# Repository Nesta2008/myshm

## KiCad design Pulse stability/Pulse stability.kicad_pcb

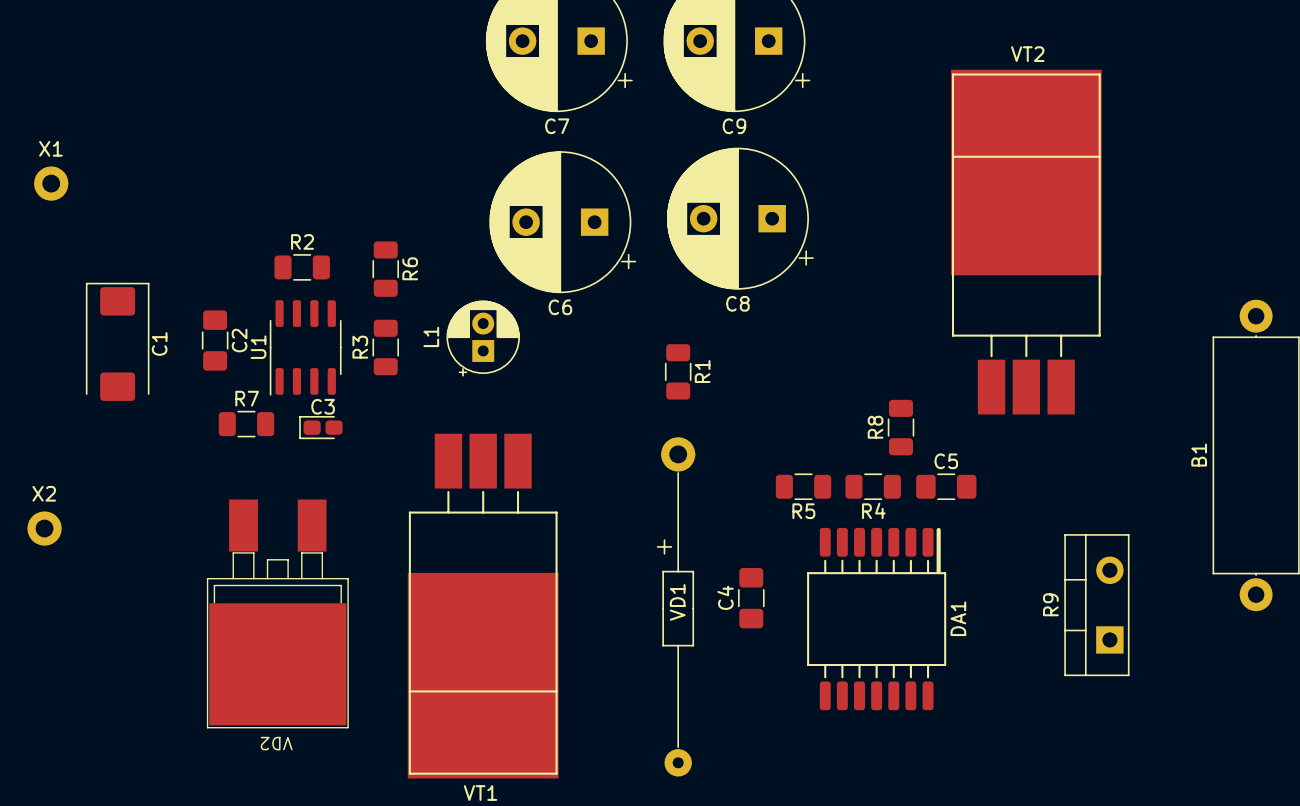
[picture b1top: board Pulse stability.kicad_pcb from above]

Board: 2 copper layers, 28 parts (0 on the bottom side), 16 nets, no tracks yet.

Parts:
B1: thermocouple; R_Axial_DIN0617_L17.0mm_D6.0mm_P20.32mm_Horizontal
C1: 15; CP_EIA-7343-40_Kemet-Y
C2, C4, C5: 0.15; C_1206_3216Metric_Pad1.42x1.75mm_HandSolder
C3: 8p; CP_EIA-1608-08_AVX-J_Pad1.25x1.05mm_HandSolder
C6, C7, C8, C9: 680; CP_Radial_D10.0mm_P5.00mm
DA1: 1486УД3; 401.14-5
L1: 27мк; CP_Radial_D5.0mm_P2.00mm
R1, R4: 510; R_1206_3216Metric
R2: 0.5; R_1206_3216Metric
R3: 12.5k; R_1206_3216Metric
R5: 360; R_1206_3216Metric
R6: 107.5k; R_1206_3216Metric
R7, R8: 1k; R_1206_3216Metric
R9: 1 Ом 20 Вт; TO-220-2_Vertical
U1: MC34063ABD-TR; SOIC-8_3.9x4.9mm_P1.27mm
VD1: Д818Е; Д818Д_P22.50mm_Pad0.8mm
VD2: VD_Schottky; КТ-90
VT1, VT2: КТ805АМ; КТ-28А-2.02_Horizontal_smd
X1: +27V; 2,5x1,3
X2: -27V; 2,5x1,3

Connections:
+12V: C5.1, C6.1, C7.1, C8.1, C9.1, DA1.4, L1.2, R1.1, R6.1
+27V: C1.1, C2.1, R2.2, U1.6, X1.1
GND: C1.2, C2.2, C3.2, C4.2, C5.2, C6.2, C7.2, C8.2, C9.2, DA1.7, DA1.8, DA1.11, DA1.14, R3.1, R5.2, R7.1, R9.2, U1.2, U1.4, VD1.2, VD2.2, X2.1
unnamed: C3.1, U1.3
unnamed: C4.1, R1.2, R4.1, VD1.1
unnamed: DA1.1, R8.1
unnamed: DA1.2, R9.1, VT2.2
unnamed: DA1.3, R4.2, R5.1
unnamed: DA1.5, DA1.6
unnamed: DA1.9, DA1.10
unnamed: DA1.12, DA1.13
unnamed: L1.1, VD2.1, VT1.2
unnamed: R2.1, U1.7, VT1.3
unnamed: R3.2, R6.2, U1.5
unnamed: R7.2, U1.1, U1.8, VT1.1
unnamed: R8.2, VT2.1

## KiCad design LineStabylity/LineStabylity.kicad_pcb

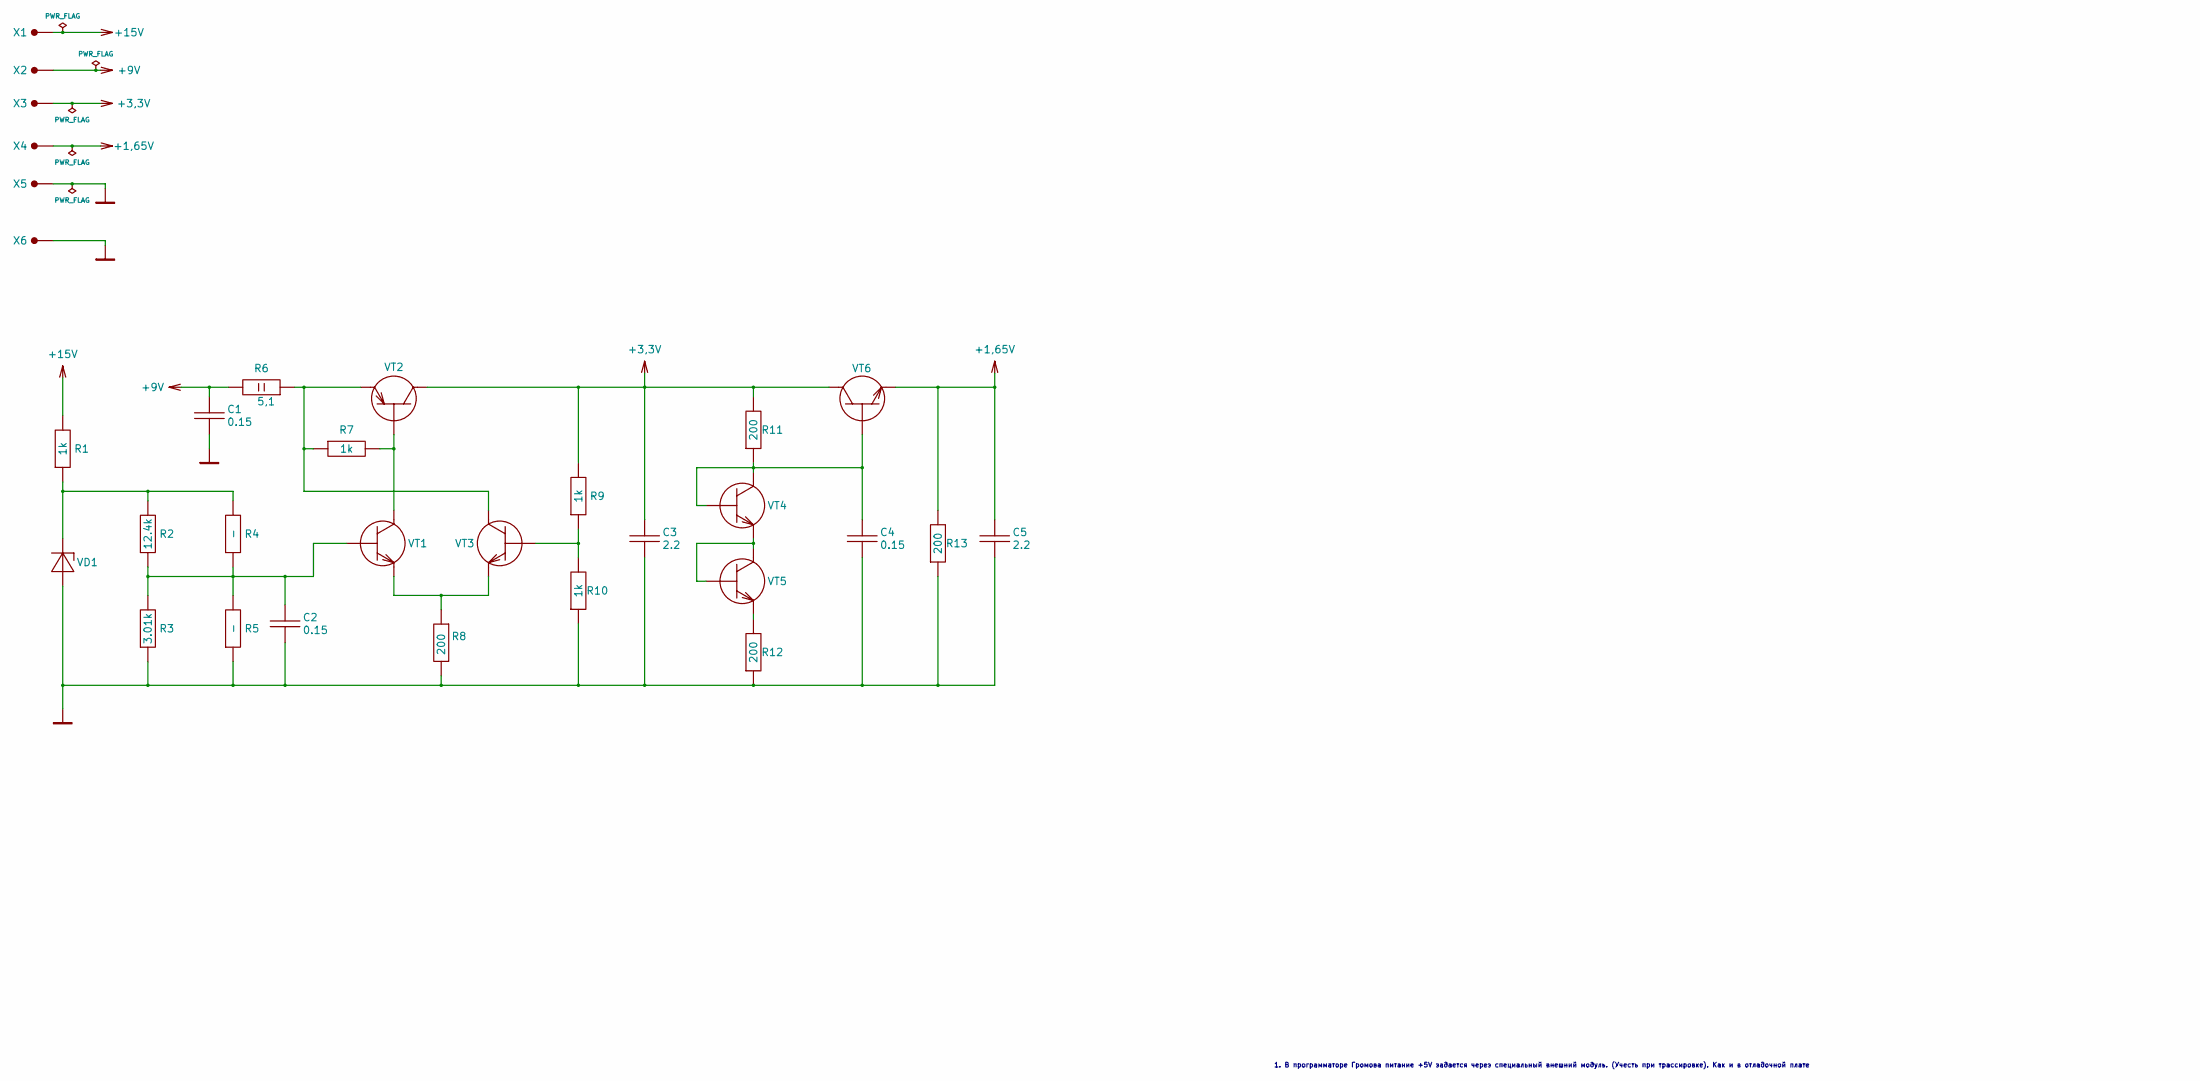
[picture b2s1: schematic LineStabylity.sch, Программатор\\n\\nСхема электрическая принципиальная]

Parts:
C1, C2, C4: 0.15; C_0805_2012Metric_Pad1.15x1.40mm_HandSolder
C3, C5: 2.2; C_2220_5650Metric
R1, R7, R9, R10: 1k; R_0805_2012Metric_Pad1.15x1.40mm_HandSolder
R2: 12.4k; R_0805_2012Metric_Pad1.15x1.40mm_HandSolder
R3: 3.01k; R_0805_2012Metric_Pad1.15x1.40mm_HandSolder
R4, R5: -; R_0805_2012Metric_Pad1.15x1.40mm_HandSolder
R6: 5,1; R_4020_10251Metric
R8, R11, R12, R13: 200; R_0805_2012Metric_Pad1.15x1.40mm_HandSolder
VD1: Д818Е; D_DO-15_P12.70mm_Horizontal
VT1, VT3, VT4, VT5, VT6: 2Т3130А9; SOT-23
VT2: 2Т664А9; SOT-89-3
X1, X2, X3, X4, X5, X6: CON; SolderWirePad_single_2.5x1.3mmDrill

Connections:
+1,65V: C5.1, R13.2, VT6.2 (E), X4.1
+3,3V: C3.1, R9.2, R11.2, VT2.2 (C), VT6.3 (C), X3.1
+9V: C1.1, R6.2, X2.1
+15V: R1.2, X1.1
GND: C1.2, C2.2, C3.2, C4.2, C5.2, R3.1, R5.1, R8.2, R10.1, R12.1, R13.1, VD1.2 (A), X5.1, X6.1
unnamed: C2.1, R2.1, R3.2, R4.1, R5.2, VT1.1 (B)
unnamed: C4.1, R11.1, VT4.1 (B), VT4.3 (C), VT6.1 (B)
unnamed: R1.1, R2.2, R4.2, VD1.1 (K)
unnamed: R6.1, R7.1, VT2.3 (E), VT3.3 (C)
unnamed: R7.2, VT1.3 (C), VT2.1 (B)
unnamed: R8.1, VT1.2 (E), VT3.2 (E)
unnamed: R9.1, R10.2, VT3.1 (B)
unnamed: R12.2, VT5.2 (E)
unnamed: VT4.2 (E), VT5.1 (B), VT5.3 (C)

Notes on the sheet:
1. В программаторе Громова питание +5V задается через специальный внешний модуль. (Учесть при трассировке). Как и в отладочной плате

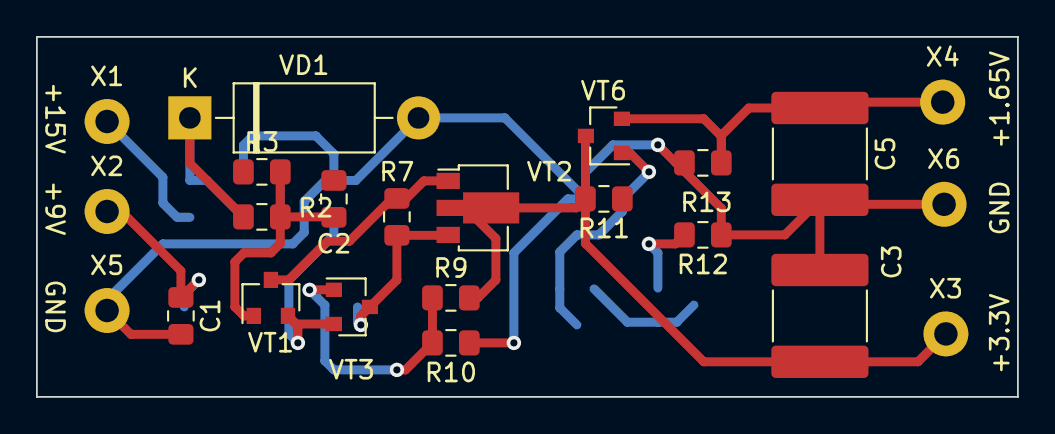
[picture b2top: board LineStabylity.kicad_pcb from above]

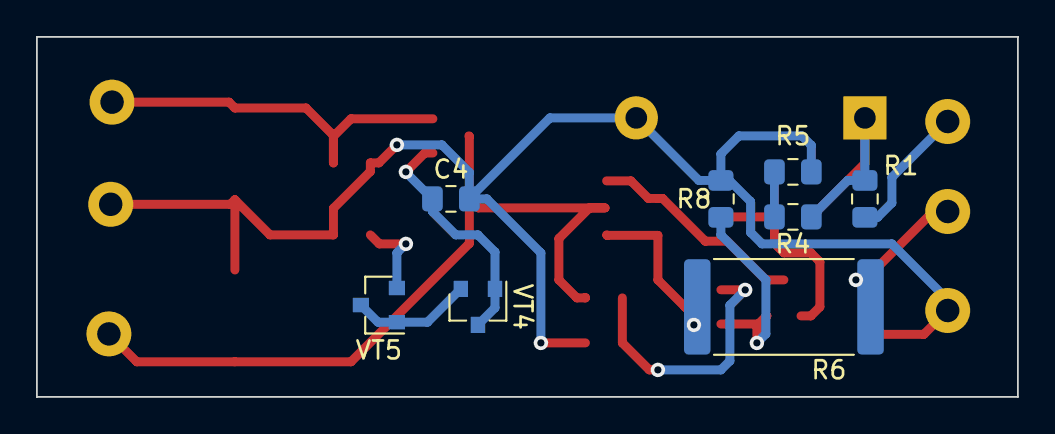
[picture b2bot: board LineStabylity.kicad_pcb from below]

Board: 2 copper layers, 54.5 x 20.0 mm, 31 parts (8 on the bottom side), 14 nets.

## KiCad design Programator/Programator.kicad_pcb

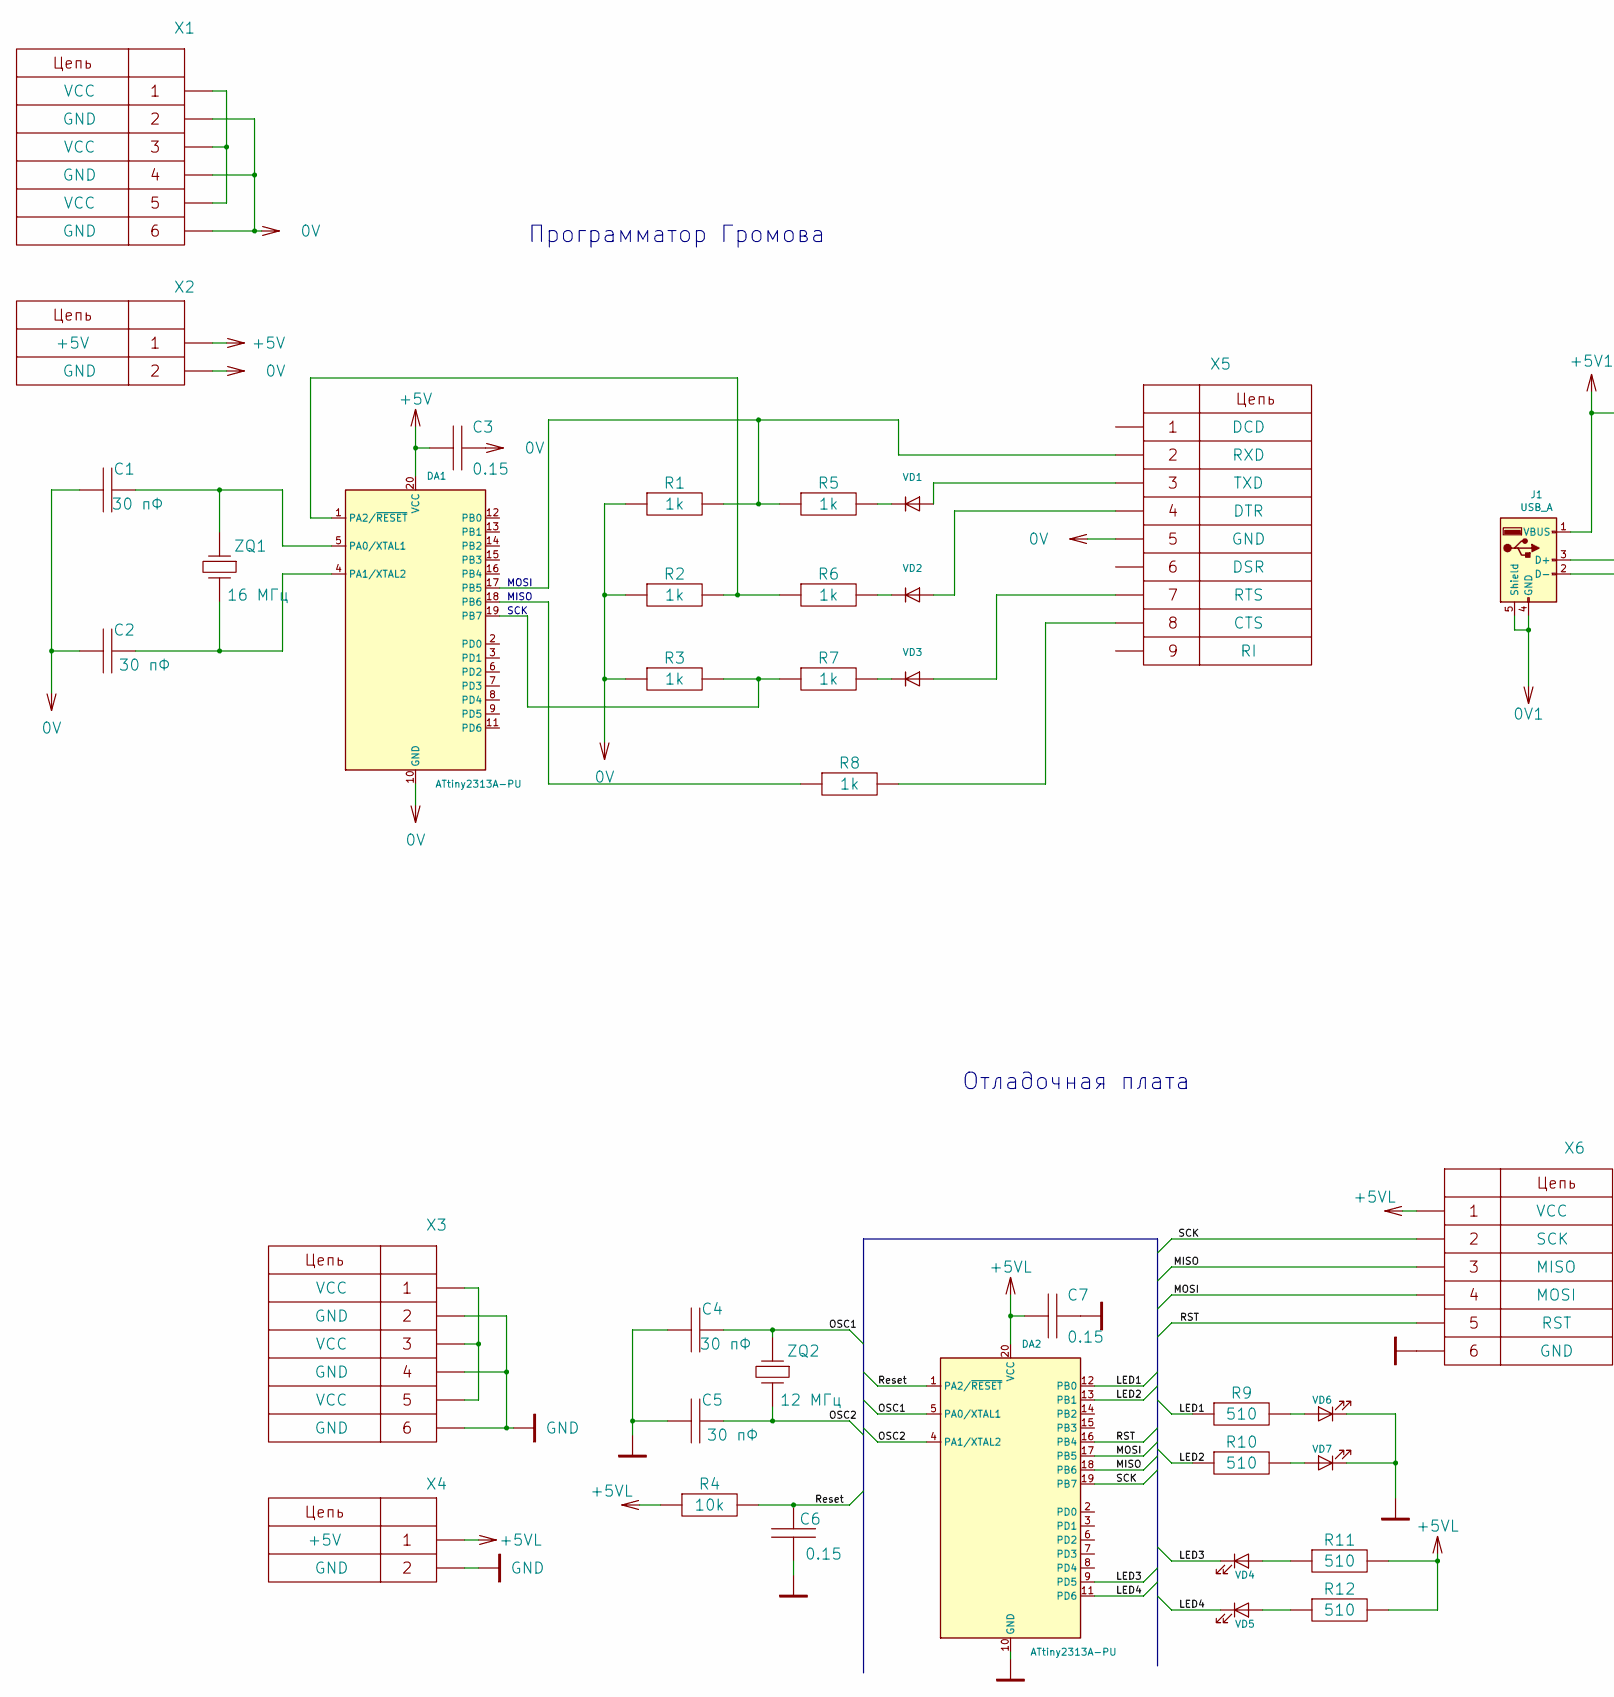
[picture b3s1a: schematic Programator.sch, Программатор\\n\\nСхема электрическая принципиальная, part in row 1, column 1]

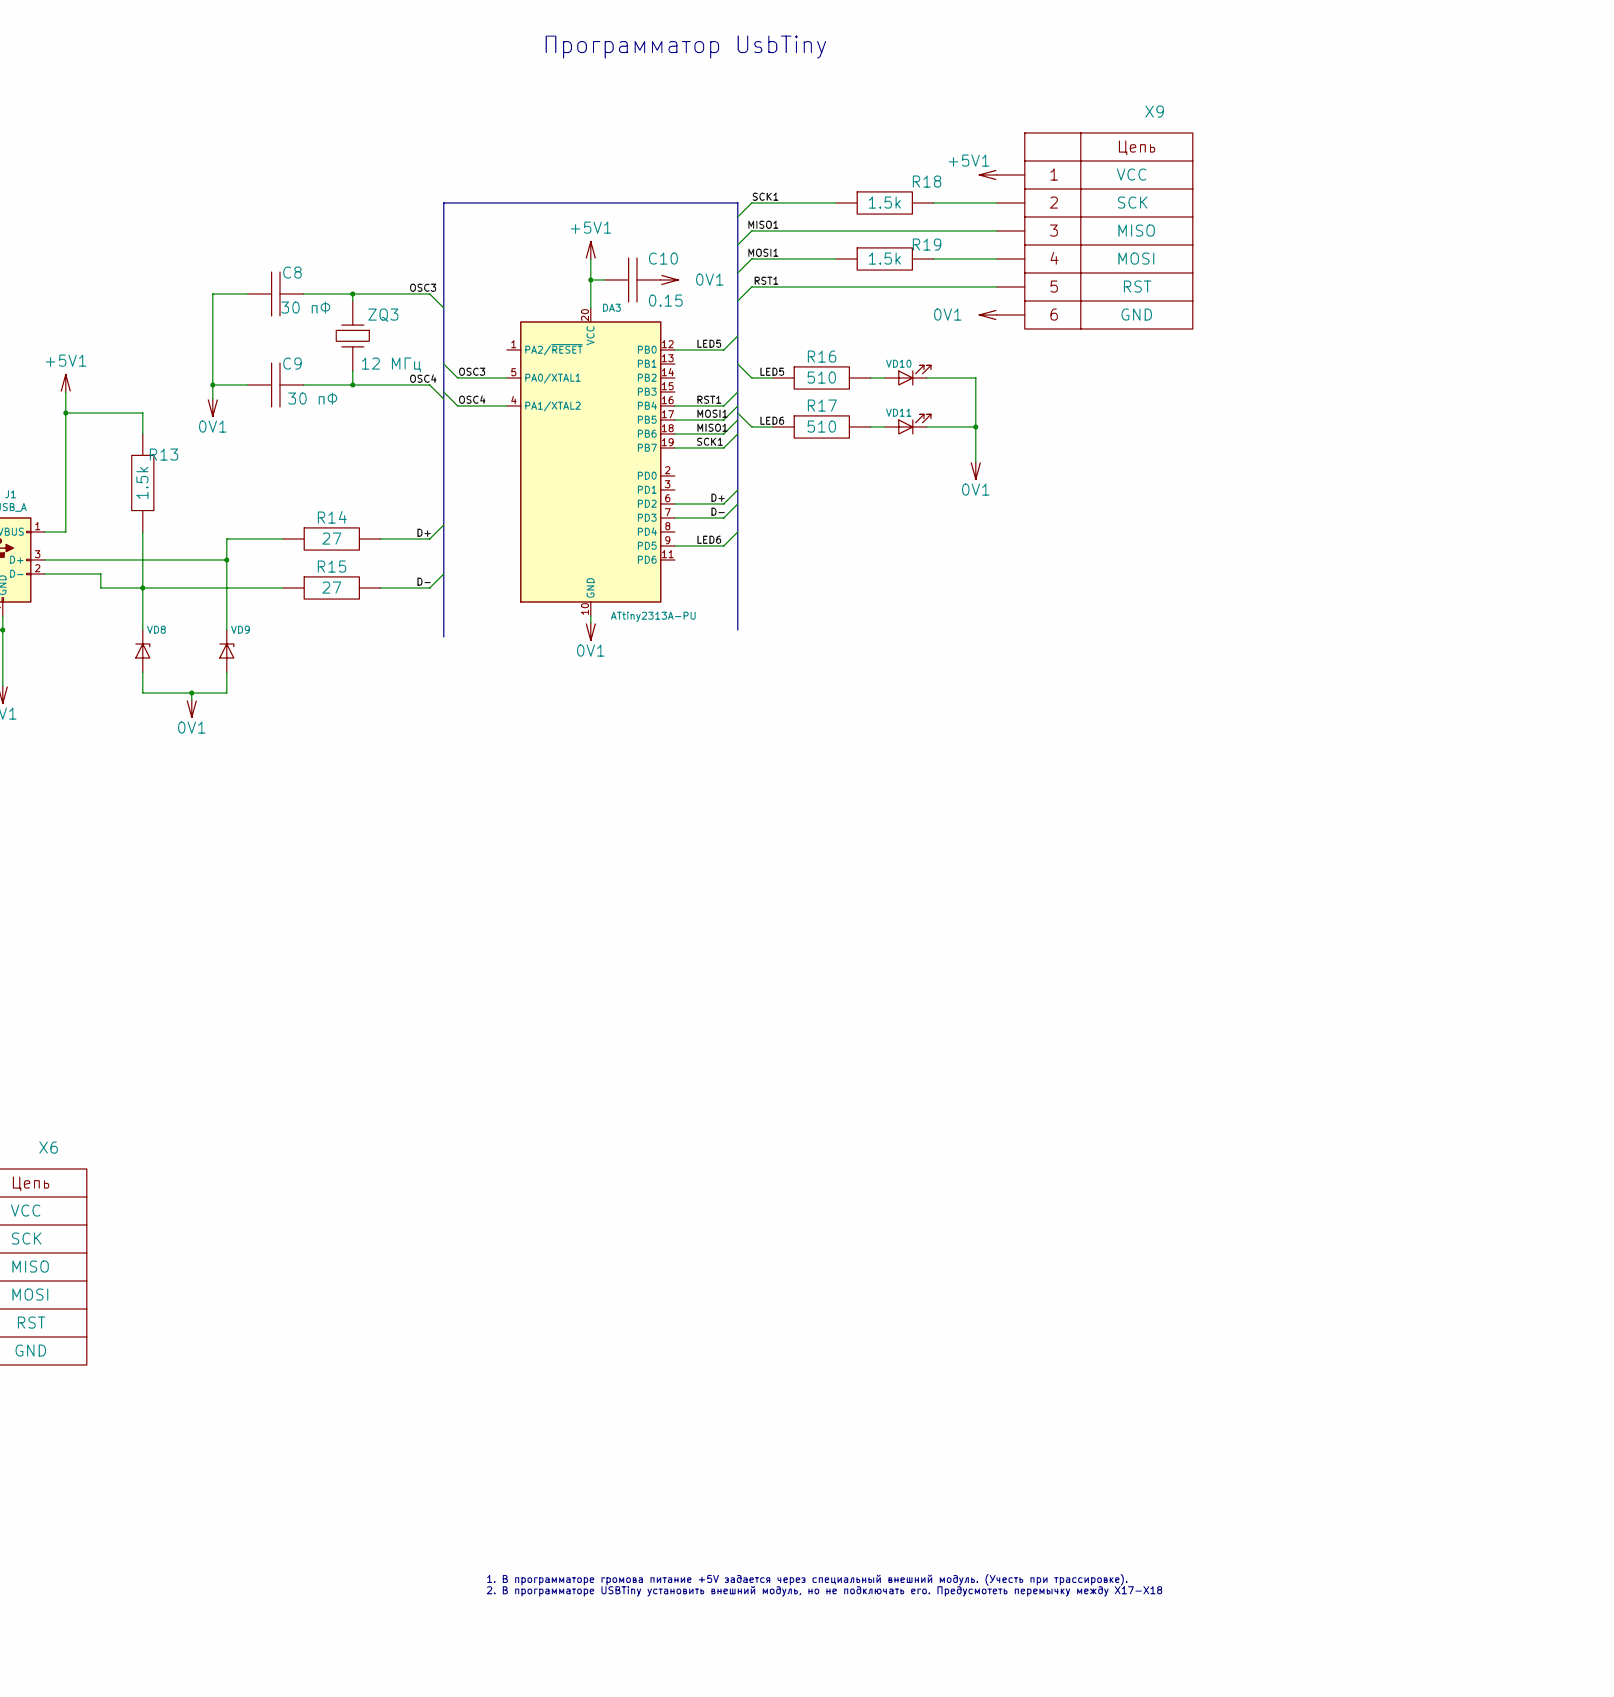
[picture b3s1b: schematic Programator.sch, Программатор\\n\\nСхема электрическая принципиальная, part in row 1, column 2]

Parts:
C1, C2, C4, C5, C8, C9: 30 пФ; C_1206_3216Metric
C3, C6, C7, C10: 0.15; C_1206_3216Metric
DA1, DA2, DA3: ATtiny2313A-PU; DIP-20_W7.62mm
J1: USB_A; USB_A_CNCTech_1001-011-01101_Horizontal
R1, R2, R3, R5, R6, R7, R8: 1k; R_1206_3216Metric
R4: 10k; R_1206_3216Metric
R9, R10, R11, R12, R16, R17: 510; R_1206_3216Metric
R13, R18, R19: 1.5k; R_1206_3216Metric
R14, R15: 27; R_1206_3216Metric
VD1, VD2, VD3: КД510А; D_DO-35_SOD27_P10.16mm_Horizontal
VD4, VD5, VD6, VD7, VD10, VD11: LED; LED_D1.8mm_W1.8mm_H2.4mm_Horizontal_O1.27mm_Z4.9mm
VD8, VD9: BZX55C3V6; D_DO-35_SOD27_P10.16mm_Horizontal
X1, X3: CONN_2; PinHeader_2x03_P2.54mm_Vertical
X2, X4: CONN_2; PinHeader_1x02_P2.54mm_Vertical
X5: CONN_9; DSUB-9_Male_Horizontal_P2.77x2.84mm_EdgePinOffset4.94mm_Hou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
X6, X9: CONN_6; IDC-Header_2x03_P2.54mm_Vertical
ZQ1: 16 МГц; Crystal_HC49-4H_Vertical
ZQ2, ZQ3: 12 МГц; Crystal_HC49-4H_Vertical

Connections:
0V: C1.1, C2.1, C3.1, DA1.10 (GND), R1.1, R2.1, R3.1, X1.2, X1.4, X1.6, X2.2, X5.5
0V1: C8.1, C9.1, C10.1, DA3.10 (GND), J1.4 (GND), J1.5 (Shield), VD8.2 (A), VD9.2 (A), VD10.1 (K), VD11.1 (K), X9.6
+5V: C3.2, DA1.20 (VCC), X2.1
+5V1: C10.2, DA3.20 (VCC), J1.1 (VBUS), R13.1, X9.1
+5VL: C7.2, DA2.20 (VCC), R4.1, R11.2, R12.2, X4.1, X6.1
/D+: DA3.6 (PD2), R14.2
/D-: DA3.7 (PD3), R15.2
/LED1: DA2.12 (PB0), R9.1
/LED2: DA2.13 (PB1), R10.1
/LED3: DA2.9 (PD5), VD4.1 (K)
/LED4: DA2.11 (PD6), VD5.1 (K)
/LED5: DA3.12 (PB0), R16.1
/LED6: DA3.9 (PD5), R17.1
/MISO: DA2.18 (PB6), X6.3
/MISO1: DA3.18 (PB6), X9.3
/MOSI: DA2.17 (PB5), X6.4
/MOSI1: DA3.17 (PB5), R19.1
/OSC1: C4.2, DA2.5 (PA0/XTAL1), ZQ2.1
/OSC2: C5.2, DA2.4 (PA1/XTAL2), ZQ2.2
/OSC3: C8.2, DA3.5 (PA0/XTAL1), ZQ3.1
/OSC4: C9.2, DA3.4 (PA1/XTAL2), ZQ3.2
/RST: DA2.16 (PB4), X6.5
/RST1: DA3.16 (PB4), X9.5
/Reset: C6.2, DA2.1 (PA2/~RESET), R4.2
/SCK: DA2.19 (PB7), X6.2
/SCK1: DA3.19 (PB7), R18.1
GND: C4.1, C5.1, C6.1, C7.1, DA2.10 (GND), VD6.1 (K), VD7.1 (K), X3.2, X3.4, X3.6, X4.2, X6.6
unnamed: C1.2, DA1.5 (PA0/XTAL1), ZQ1.1
unnamed: C2.2, DA1.4 (PA1/XTAL2), ZQ1.2
unnamed: DA1.1 (PA2/~RESET), R2.2, R6.1
unnamed: DA1.17 (PB5), R1.2, R5.1, X5.2
unnamed: DA1.18 (PB6), R8.1
unnamed: DA1.19 (PB7), R3.2, R7.1
unnamed: J1.2 (D-), R13.2, R15.1, VD8.1 (K)
unnamed: J1.3 (D+), R14.1, VD9.1 (K)
unnamed: R5.2, VD1.1 (K)
unnamed: R6.2, VD2.1 (K)
unnamed: R7.2, VD3.1 (K)
unnamed: R8.2, X5.8
unnamed: R9.2, VD6.2 (A)
unnamed: R10.2, VD7.2 (A)
unnamed: R11.1, VD4.2 (A)
unnamed: R12.1, VD5.2 (A)
unnamed: R16.2, VD10.2 (A)
unnamed: R17.2, VD11.2 (A)
unnamed: R18.2, X9.2
unnamed: R19.2, X9.4
unnamed: VD1.2 (A), X5.3
unnamed: VD2.2 (A), X5.4
unnamed: VD3.2 (A), X5.7
unnamed: X1.1, X1.3, X1.5
unnamed: X3.1, X3.3, X3.5

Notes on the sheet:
MISO
MOSI
SCK
Программатор Громова
Программатор UsbTiny
Отладочная плата
1. В программаторе громова питание +5V задается через специальный внешний модуль. (Учесть при трассировке). 2. В программаторе USBTiny установить внешний модуль, но не подключать его. Предусмотеть перемычку между X17-X18

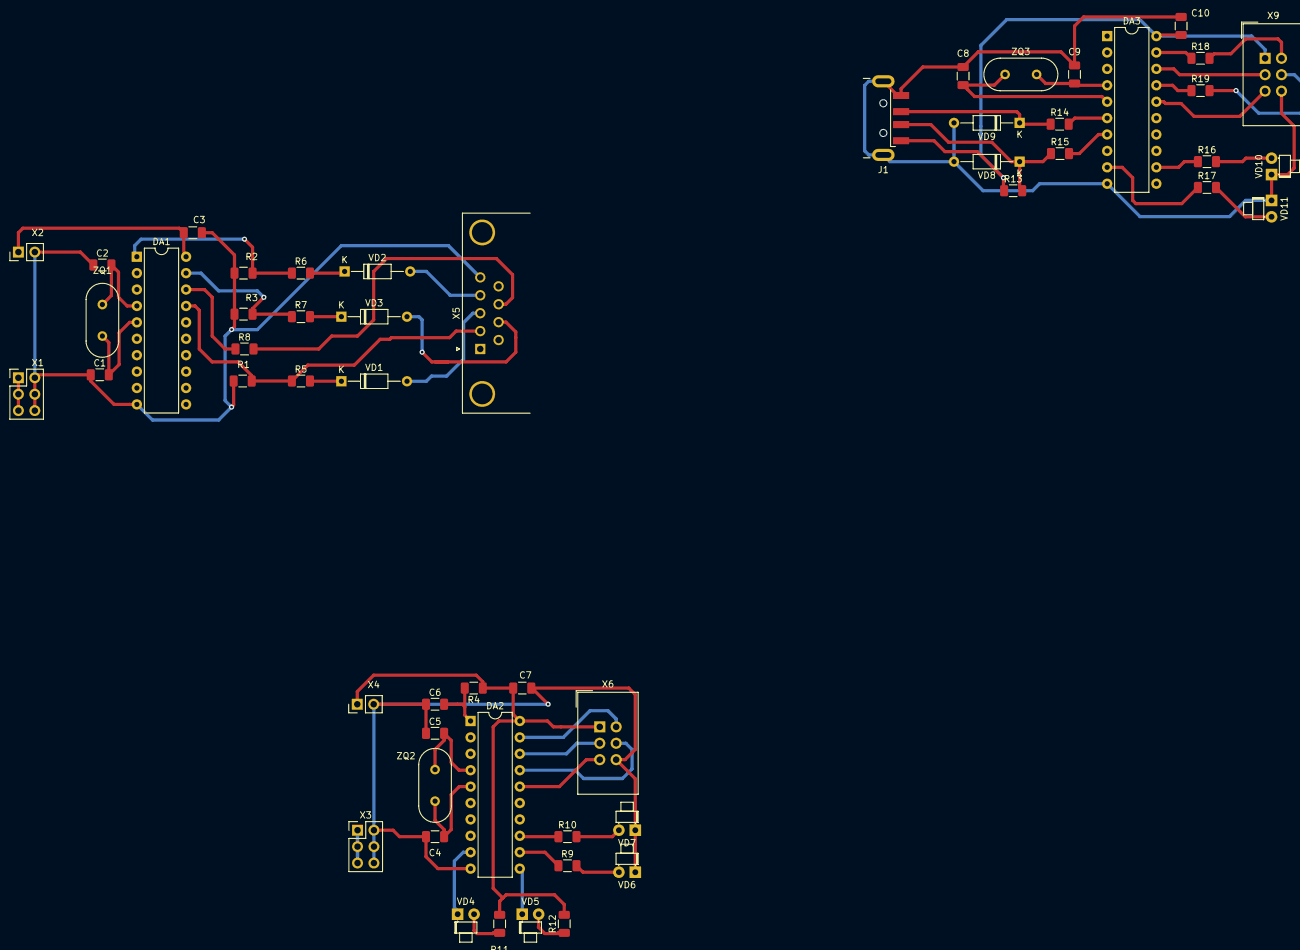
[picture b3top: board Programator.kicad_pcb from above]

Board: 2 copper layers, 54 parts (0 on the bottom side), 52 nets.
